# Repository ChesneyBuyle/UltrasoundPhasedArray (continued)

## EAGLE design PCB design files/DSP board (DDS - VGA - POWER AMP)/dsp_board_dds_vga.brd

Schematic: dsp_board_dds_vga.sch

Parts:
C1, C2, C3, C8, C13, C14, C19, C20, C25, C26, C31, C32, C37, C38, C43, C44, C49, C50, C55, C56, C61, C62, C67, C68, C73, C74, C79, C80, C86, C91, C92, C97, C98, C106, C113, C119, C121, C127, C129, C135, C137, C143, C145, C151, C153, C159, C161, C167, C169, C175, C177, C183, C185, C191, C193, C199, C201, C207, C209, C215, C217, C223, C225, C231: 0.1u; C0603
C4, C5, C9, C10, C15, C16, C21, C22, C27, C28, C33, C34, C39, C40, C45, C46, C51, C52, C57, C58, C63, C64, C69, C70, C75, C76, C81, C82, C93, C94, C99, C100: 10n; C0603
C6, C11, C17, C23, C29, C35, C41, C47, C53, C59, C65, C71, C77, C83, C95, C101: 20p; C0603
C7, C12, C18, C24, C30, C36, C42, C48, C54, C60, C66, C72, C78, C84, C96, C102: TBD; C0603
C87, C88, C89, C90, C107, C114, C115, C116, C117, C120, C122, C123, C124, C125, C128, C130, C131, C132, C133, C136, C138, C139, C140, C141, C144, C146, C147, C148, C149, C152, C154, C155, C156, C157, C160, C162, C163, C164, C165, C168, C170, C171, C172, C173, C176, C178, C179, C180, C181, C184, C186, C187, C188, C189, C192, C194, C195, C196, C197, C200, C202, C203, C204, C205, C208, C210, C211, C212, C213, C216, C218, C219, C220, C221, C224, C226, C227, C228, C229, C232: 1u; C0603
C104, C118, C126, C134, C142, C150, C158, C166, C174, C182, C190, C198, C206, C214, C222, C230: 10u; C0805
H1, H2: MOUNT-HOLE3.0; 3,0
IC1, IC2, IC3, IC4, IC5, IC6, IC7, IC8, IC9, IC10, IC11, IC12, IC13, IC14, IC16, IC17: AD9834; TSSOP20
J1, J4: 6130XX21021_61301421021; 61301421021
J2, J7: 6130XX21021_61301621021; 61301621021
JP1, JP2, JP3, JP4, JP5, JP6, JP7, JP8, JP9, JP10, JP11, JP12, JP13, JP14, JP15, JP16: PINHD-1X2; 1X02
LDO, LDO2, LDO3, LDO4, LDO5, LDO6, LDO7, LDO8, LDO9, LDO10, LDO11, LDO12, LDO13, LDO14, LDO15, LDO16: TLV75525PDBVR; SOT95P280X145-5N
LSP1, LSP2, LSP3, LSP4, LSP5, LSP6, LSP7, LSP8, LSP9, LSP10, LSP11, LSP12, LSP13, LSP14, LSP15, LSP16, LSP17, LSP18, LSP19, LSP20: LSP10
R1, R2, R9, R13, R17, R21, R25, R29, R33, R37, R41, R45, R49, R53, R61, R65: 6.8k; R0603
R3, R8, R12, R16, R20, R24, R28, R32, R36, R40, R44, R48, R52, R56, R64, R68: TBD; R0603
R4, R5, R6, R7, R10, R11, R14, R15, R18, R19, R22, R23, R26, R27, R30, R31, R34, R35, R38, R39, R42, R43, R46, R47, R50, R51, R54, R55, R62, R63, R66, R67: 200; R0603
R57, R59, R60, R69, R70, R71, R72, R73, R74, R75, R76, R77, R78, R79, R80, R81: R-EU_R0603; R0603
SJ1, SJ2, SJ3, SJ4, SJ5, SJ6, SJ7, SJ8, SJ9, SJ10, SJ11, SJ12, SJ13, SJ14, SJ15, SJ16, SJ17, SJ18, SJ19, SJ20, SJ21, SJ22, SJ23, SJ24, SJ25, SJ26, SJ27, SJ28, SJ29, SJ30, SJ31, SJ32, SJ33, SJ34, SJ35, SJ36, SJ37, SJ38, SJ39, SJ40, SJ41, SJ42, SJ43, SJ44, SJ45, SJ46, SJ47, SJ48, SJ49, SJ50, SJ51, SJ52, SJ53, SJ54, SJ55, SJ56, SJ57, SJ58, SJ59, SJ60, SJ61, SJ62, SJ63, SJ64, SJ65, SJ66, SJ67, SJ68, SJ69, SJ70, SJ71, SJ72, SJ73, SJ74, SJ75, SJ76, SJ77, SJ78, SJ79, SJ80, SJ81, SJ82, SJ83, SJ84, SJ91, SJ92, SJ93, SJ94, SJ95, SJ96, SJ97, SJ98, SJ99, SJ100, SJ101, SJ102: SJ
U1, U7, U10, U13, U16, U19, U22, U25, U28, U31, U34, U37, U40, U43, U46, U49: TPS60400DBVT; SOT95P280X145-5N
U2, U9, U12, U15, U18, U21, U24, U27, U30, U33, U36, U39, U42, U45, U48, U51: TLV271CDBVR; SOT95P280X145-5N
U3, U8, U11, U14, U17, U20, U23, U26, U29, U32, U35, U38, U41, U44, U47, U50: AD5270BRMZ-50; SOP50P490X110-10N

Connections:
2.5V_1: C86.2, C89.2, C104.1, LDO.5 (OUT), U1.2 (IN), U2.5 (VDD), U3.1 (VDD)
2.5V_2: C113.2, C116.2, C118.1, LDO2.5 (OUT), U7.2 (IN), U8.1 (VDD), U9.5 (VDD)
2.5V_3: C137.2, C140.2, C142.1, LDO5.5 (OUT), U16.2 (IN), U17.1 (VDD), U18.5 (VDD)
2.5V_4: C145.2, C148.2, C150.1, LDO6.5 (OUT), U19.2 (IN), U20.1 (VDD), U21.5 (VDD)
2.5V_5: C121.2, C124.2, C126.1, LDO3.5 (OUT), U10.2 (IN), U11.1 (VDD), U12.5 (VDD)
2.5V_6: C129.2, C132.2, C134.1, LDO4.5 (OUT), U13.2 (IN), U14.1 (VDD), U15.5 (VDD)
2.5V_7: C153.2, C156.2, C158.1, LDO7.5 (OUT), U22.2 (IN), U23.1 (VDD), U24.5 (VDD)
2.5V_8: C161.2, C164.2, C166.1, LDO8.5 (OUT), U25.2 (IN), U26.1 (VDD), U27.5 (VDD)
2.5V_9: C169.2, C172.2, C174.1, LDO9.5 (OUT), U28.2 (IN), U29.1 (VDD), U30.5 (VDD)
2.5V_10: C177.2, C180.2, C182.1, LDO10.5 (OUT), U31.2 (IN), U32.1 (VDD), U33.5 (VDD)
2.5V_11: C201.2, C204.2, C206.1, LDO13.5 (OUT), U40.2 (IN), U41.1 (VDD), U42.5 (VDD)
2.5V_12: C209.2, C212.2, C214.1, LDO14.5 (OUT), U43.2 (IN), U44.1 (VDD), U45.5 (VDD)
2.5V_13: C185.2, C188.2, C190.1, LDO11.5 (OUT), U34.2 (IN), U35.1 (VDD), U36.5 (VDD)
2.5V_14: C193.2, C196.2, C198.1, LDO12.5 (OUT), U37.2 (IN), U38.1 (VDD), U39.5 (VDD)
2.5V_15: C217.2, C220.2, C222.1, LDO15.5 (OUT), U46.2 (IN), U47.1 (VDD), U48.5 (VDD)
2.5V_16: C225.2, C228.2, C230.1, LDO16.5 (OUT), U49.2 (IN), U50.1 (VDD), U51.5 (VDD)
+3V3: C1.1, C2.1, C5.2, C10.2, C13.1, C16.2, C19.1, C22.2, C25.1, C28.2, C31.1, C34.2, C37.1, C40.2, C43.1, C46.2, C49.1, C52.2, C55.1, C58.2, C61.1, C64.2, C67.1, C70.2, C73.1, C76.2, C79.1, C82.2, C87.2, C91.1, C94.2, C97.1, C100.2, C114.2, C122.2, C130.2, C138.2, C146.2, C154.2, C162.2, C170.2, C178.2, C186.2, C194.2, C202.2, C210.2, C218.2, C226.2, IC1.4 (AVDD), IC1.5 (DVDD), IC2.4 (AVDD), IC2.5 (DVDD), IC3.4 (AVDD), IC3.5 (DVDD), IC4.4 (AVDD), IC4.5 (DVDD), IC5.4 (AVDD), IC5.5 (DVDD), IC6.4 (AVDD), IC6.5 (DVDD), IC7.4 (AVDD), IC7.5 (DVDD), IC8.4 (AVDD), IC8.5 (DVDD), IC9.4 (AVDD), IC9.5 (DVDD), IC10.4 (AVDD), IC10.5 (DVDD), IC11.4 (AVDD), IC11.5 (DVDD), IC12.4 (AVDD), IC12.5 (DVDD), IC13.4 (AVDD), IC13.5 (DVDD), IC14.4 (AVDD), IC14.5 (DVDD), IC16.4 (AVDD), IC16.5 (DVDD), IC17.4 (AVDD), IC17.5 (DVDD), J2.1, J7.1, LDO.1 (IN), LDO.3 (EN), LDO2.1 (IN), LDO2.3 (EN), LDO3.1 (IN), LDO3.3 (EN), LDO4.1 (IN), LDO4.3 (EN), LDO5.1 (IN), LDO5.3 (EN), LDO6.1 (IN), LDO6.3 (EN), LDO7.1 (IN), LDO7.3 (EN), LDO8.1 (IN), LDO8.3 (EN), LDO9.1 (IN), LDO9.3 (EN), LDO10.1 (IN), LDO10.3 (EN), LDO11.1 (IN), LDO11.3 (EN), LDO12.1 (IN), LDO12.3 (EN), LDO13.1 (IN), LDO13.3 (EN), LDO14.1 (IN), LDO14.3 (EN), LDO15.1 (IN), LDO15.3 (EN), LDO16.1 (IN), LDO16.3 (EN)
DDS1_OUT: R57.1, SJ1.2, SJ2.2
DDS2_OUT: R59.1, SJ6.2, SJ8.2
DDS3_OUT: R70.1, SJ13.2, SJ14.2
DDS4_OUT: R71.1, SJ19.2, SJ20.2
DDS5_OUT: R60.1, SJ25.2, SJ26.2
DDS6_OUT: R69.1, SJ31.2, SJ32.2
DDS7_OUT: R72.1, SJ37.2, SJ38.2
DDS8_OUT: R73.1, SJ43.2, SJ44.2
DDS9_OUT: R74.1, SJ49.2, SJ50.2
DDS10_OUT: R75.1, SJ55.2, SJ56.2
DDS11_OUT: R78.1, SJ61.2, SJ62.2
DDS12_OUT: R79.1, SJ67.2, SJ68.2
DDS13_OUT: R76.1, SJ73.2, SJ74.2
DDS14_OUT: R77.1, SJ91.2, SJ92.2
DDS15_OUT: R80.1, SJ79.2, SJ80.2
DDS16_OUT: R81.1, SJ97.2, SJ98.2
DIN_2_A: J2.12, U3.8 (DIN), U8.8 (DIN), U17.8 (DIN), U20.8 (DIN)
DIN_2_B: J4.10, U11.8 (DIN), U14.8 (DIN), U23.8 (DIN), U26.8 (DIN)
DIN_2_C: J1.10, U29.8 (DIN), U32.8 (DIN), U41.8 (DIN), U44.8 (DIN)
DIN_2_D: J7.12, U35.8 (DIN), U38.8 (DIN), U47.8 (DIN), U50.8 (DIN)
FILTER1: C7.1, R3.2, SJ1.1, SJ4.2, SJ5.2
FILTER2: C12.1, R8.2, SJ6.1, SJ11.2, SJ12.2
FILTER3: C18.1, R12.2, SJ13.1, SJ17.2, SJ18.2
FILTER4: C24.1, R16.2, SJ19.1, SJ23.2, SJ24.2
FILTER5: C30.1, R20.2, SJ25.1, SJ29.2, SJ30.2
FILTER6: C36.1, R24.2, SJ31.1, SJ35.2, SJ36.2
FILTER7: C42.1, R28.2, SJ37.1, SJ41.2, SJ42.2
FILTER8: C48.1, R32.2, SJ43.1, SJ47.2, SJ48.2
FILTER9: C54.1, R36.2, SJ49.1, SJ53.2, SJ54.2
FILTER10: C60.1, R40.2, SJ55.1, SJ59.2, SJ60.2
FILTER11: C66.1, R44.2, SJ61.1, SJ65.2, SJ66.2
FILTER12: C72.1, R48.2, SJ67.1, SJ71.2, SJ72.2
FILTER13: C78.1, R52.2, SJ73.1, SJ77.2, SJ78.2
FILTER14: C96.1, R64.2, SJ91.1, SJ95.2, SJ96.2
FILTER15: C84.1, R56.2, SJ79.1, SJ83.2, SJ84.2
FILTER16: C102.1, R68.2, SJ97.1, SJ101.2, SJ102.2
FSELECT_A: IC1.9 (FSELECT), IC2.9 (FSELECT), IC3.9 (FSELECT), IC4.9 (FSELECT), J2.3
FSELECT_B: IC5.9 (FSELECT), IC6.9 (FSELECT), IC7.9 (FSELECT), IC8.9 (FSELECT), J4.1
FSELECT_C: IC9.9 (FSELECT), IC10.9 (FSELECT), IC11.9 (FSELECT), IC12.9 (FSELECT), J1.1
FSELECT_D: IC13.9 (FSELECT), IC14.9 (FSELECT), IC16.9 (FSELECT), IC17.9 (FSELECT), J7.3
FSYNC1: IC1.15 (FSYNC), J2.5, U3.10 (~SYNC)
FSYNC2: IC2.15 (FSYNC), J2.8, U8.10 (~SYNC)
FSYNC3: IC3.15 (FSYNC), J2.7, U17.10 (~SYNC)
FSYNC4: IC4.15 (FSYNC), J2.10, U20.10 (~SYNC)
FSYNC5: IC5.15 (FSYNC), J4.3, U11.10 (~SYNC)
FSYNC6: IC6.15 (FSYNC), J4.6, U14.10 (~SYNC)
FSYNC7: IC7.15 (FSYNC), J4.5, U23.10 (~SYNC)
FSYNC8: IC8.15 (FSYNC), J4.8, U26.10 (~SYNC)
FSYNC9: IC9.15 (FSYNC), J1.3, U29.10 (~SYNC)
FSYNC10: IC10.15 (FSYNC), J1.6, U32.10 (~SYNC)
FSYNC11: IC11.15 (FSYNC), J1.5, U41.10 (~SYNC)
FSYNC12: IC12.15 (FSYNC), J1.8, U44.10 (~SYNC)
FSYNC13: IC13.15 (FSYNC), J7.5, U35.10 (~SYNC)
FSYNC14: IC16.15 (FSYNC), J7.8, U38.10 (~SYNC)
FSYNC15: IC14.15 (FSYNC), J7.7, U47.10 (~SYNC)
FSYNC16: IC17.15 (FSYNC), J7.10, U50.10 (~SYNC)
GND: C1.2, C2.2, C3.2, C4.2, C6.2, C7.2, C8.2, C9.2, C11.2, C12.2, C13.2, C14.2, C15.2, C17.2, C18.2, C19.2, C20.2, C21.2, C23.2, C24.2, C25.2, C26.2, C27.2, C29.2, C30.2, C31.2, C32.2, C33.2, C35.2, C36.2, C37.2, C38.2, C39.2, C41.2, C42.2, C43.2, C44.2, C45.2, C47.2, C48.2, C49.2, C50.2, C51.2, C53.2, C54.2, C55.2, C56.2, C57.2, C59.2, C60.2, C61.2, C62.2, C63.2, C65.2, C66.2, C67.2, C68.2, C69.2, C71.2, C72.2, C73.2, C74.2, C75.2, C77.2, C78.2, C79.2, C80.2, C81.2, C83.2, C84.2, C86.1, C87.1, C89.1, C90.1, C91.2, C92.2, C93.2, C95.2, C96.2, C97.2, C98.2, C99.2, C101.2, C102.2, C104.2, C106.2, C107.2, C113.1, C114.1, C116.1, C117.1, C118.2, C119.2, C120.2, C121.1, C122.1, C124.1, C125.1, C126.2, C127.2, C128.2, C129.1, C130.1, C132.1, C133.1, C134.2, C135.2, C136.2, C137.1, C138.1, C140.1, C141.1, C142.2, C143.2, C144.2, C145.1, C146.1, C148.1, C149.1, C150.2, C151.2, C152.2, C153.1, C154.1, C156.1, C157.1, C158.2, C159.2, C160.2, C161.1, C162.1, C164.1, C165.1, C166.2, C167.2, C168.2, C169.1, C170.1, C172.1, C173.1, C174.2, C175.2, C176.2, C177.1, C178.1, C180.1, C181.1, C182.2, C183.2, C184.2, C185.1, C186.1, C188.1, C189.1, C190.2, C191.2, C192.2, C193.1, C194.1, C196.1, C197.1, C198.2, C199.2, C200.2, C201.1, C202.1, C204.1, C205.1, C206.2, C207.2, C208.2, C209.1, C210.1, C212.1, C213.1, C214.2, C215.2, C216.2, C217.1, C218.1, C220.1, C221.1, C222.2, C223.2, C224.2, C225.1, C226.1, C228.1, C229.1, C230.2, C231.2, C232.2, IC1.7 (DGND), IC1.18 (AGND), IC2.7 (DGND), IC2.18 (AGND), IC3.7 (DGND), IC3.18 (AGND), IC4.7 (DGND), IC4.18 (AGND), IC5.7 (DGND), IC5.18 (AGND), IC6.7 (DGND), IC6.18 (AGND), IC7.7 (DGND), IC7.18 (AGND), IC8.7 (DGND), IC8.18 (AGND), IC9.7 (DGND), IC9.18 (AGND), IC10.7 (DGND), IC10.18 (AGND), IC11.7 (DGND), IC11.18 (AGND), IC12.7 (DGND), IC12.18 (AGND), IC13.7 (DGND), IC13.18 (AGND), IC14.7 (DGND), IC14.18 (AGND), IC16.7 (DGND), IC16.18 (AGND), IC17.7 (DGND), IC17.18 (AGND), J2.2, J7.2, JP1.2, JP2.2, JP3.2, JP4.2, JP5.2, JP6.2, JP7.2, JP8.2, JP9.2, JP10.2, JP11.2, JP12.2, JP13.2, JP14.2, JP15.2, JP16.2, LDO.2 (GND), LDO2.2 (GND), LDO3.2 (GND), LDO4.2 (GND), LDO5.2 (GND), LDO6.2 (GND), LDO7.2 (GND), LDO8.2 (GND), LDO9.2 (GND), LDO10.2 (GND), LDO11.2 (GND), LDO12.2 (GND), LDO13.2 (GND), LDO14.2 (GND), LDO15.2 (GND), LDO16.2 (GND), LSP1.MP, LSP2.MP, LSP3.MP, LSP4.MP, LSP5.MP, LSP6.MP, LSP7.MP, LSP8.MP, LSP9.MP, LSP10.MP, LSP11.MP, LSP12.MP, LSP13.MP, LSP14.MP, LSP15.MP, LSP16.MP, LSP17.MP, LSP18.MP, LSP19.MP, LSP20.MP, R1.2, R2.2, R4.1, R5.1, R6.1, R7.1, R9.2, R10.1, R11.1, R13.2, R14.1, R15.1, R17.2, R18.1, R19.1, R21.2, R22.1, R23.1, R25.2, R26.1, R27.1, R29.2, R30.1, R31.1, R33.2, R34.1, R35.1, R37.2, R38.1, R39.1, R41.2, R42.1, R43.1, R45.2, R46.1, R47.1, R49.2, R50.1, R51.1, R53.2, R54.1, R55.1, R61.2, R62.1, R63.1, R65.2, R66.1, R67.1, SJ3.1, SJ7.2, SJ9.1, SJ10.2, SJ15.1, SJ16.2, SJ21.1, SJ22.2, SJ27.1, SJ28.2, SJ33.1, SJ34.2, SJ39.1, SJ40.2, SJ45.1, SJ46.2, SJ51.1, SJ52.2, SJ57.1, SJ58.2, SJ63.1, SJ64.2, SJ69.1, SJ70.2, SJ75.1, SJ76.2, SJ81.1, SJ82.2, SJ93.1, SJ94.2, SJ99.1, SJ100.2, U1.4 (GND), U2.3 (IN+), U3.6 (GND), U7.4 (GND), U8.6 (GND), U9.3 (IN+), U10.4 (GND), U11.6 (GND), U12.3 (IN+), U13.4 (GND), U14.6 (GND), U15.3 (IN+), U16.4 (GND), U17.6 (GND), U18.3 (IN+), U19.4 (GND), U20.6 (GND), U21.3 (IN+), U22.4 (GND), U23.6 (GND), U24.3 (IN+), U25.4 (GND), U26.6 (GND), U27.3 (IN+), U28.4 (GND), U29.6 (GND), U30.3 (IN+), U31.4 (GND), U32.6 (GND), U33.3 (IN+), U34.4 (GND), U35.6 (GND), U36.3 (IN+), U37.4 (GND), U38.6 (GND), U39.3 (IN+), U40.4 (GND), U41.6 (GND), U42.3 (IN+), U43.4 (GND), U44.6 (GND), U45.3 (IN+), U46.4 (GND), U47.6 (GND), U48.3 (IN+), U49.4 (GND), U50.6 (GND), U51.3 (IN+)
IOUT1: IC1.19 (IOUT), R3.1, R5.2, SJ4.1
IOUT2: IC2.19 (IOUT), R7.2, R8.1, SJ11.1
IOUT3: IC3.19 (IOUT), R11.2, R12.1, SJ17.1
IOUT4: IC4.19 (IOUT), R15.2, R16.1, SJ23.1
IOUT5: IC5.19 (IOUT), R19.2, R20.1, SJ29.1
IOUT6: IC6.19 (IOUT), R23.2, R24.1, SJ35.1
IOUT7: IC7.19 (IOUT), R27.2, R28.1, SJ41.1
IOUT8: IC8.19 (IOUT), R31.2, R32.1, SJ47.1
IOUT9: IC9.19 (IOUT), R35.2, R36.1, SJ53.1
IOUT10: IC10.19 (IOUT), R39.2, R40.1, SJ59.1
IOUT11: IC11.19 (IOUT), R43.2, R44.1, SJ65.1
IOUT12: IC12.19 (IOUT), R47.2, R48.1, SJ71.1
IOUT13: IC13.19 (IOUT), R51.2, R52.1, SJ77.1
IOUT14: IC16.19 (IOUT), R63.2, R64.1, SJ95.1
IOUT15: IC14.19 (IOUT), R55.2, R56.1, SJ83.1
IOUT16: IC17.19 (IOUT), R67.2, R68.1, SJ101.1
IOUTB1: C6.1, IC1.20 (IOUTB), R4.2, SJ7.1
IOUTB2: C11.1, IC2.20 (IOUTB), R6.2, SJ10.1
IOUTB3: C17.1, IC3.20 (IOUTB), R10.2, SJ16.1
IOUTB4: C23.1, IC4.20 (IOUTB), R14.2, SJ22.1
IOUTB5: C29.1, IC5.20 (IOUTB), R18.2, SJ28.1
IOUTB6: C35.1, IC6.20 (IOUTB), R22.2, SJ34.1
IOUTB7: C41.1, IC7.20 (IOUTB), R26.2, SJ40.1
IOUTB8: C47.1, IC8.20 (IOUTB), R30.2, SJ46.1
IOUTB9: C53.1, IC9.20 (IOUTB), R34.2, SJ52.1
IOUTB10: C59.1, IC10.20 (IOUTB), R38.2, SJ58.1
IOUTB11: C65.1, IC11.20 (IOUTB), R42.2, SJ64.1
IOUTB12: C71.1, IC12.20 (IOUTB), R46.2, SJ70.1
IOUTB13: C77.1, IC13.20 (IOUTB), R50.2, SJ76.1
IOUTB14: C95.1, IC16.20 (IOUTB), R62.2, SJ94.1
IOUTB15: C83.1, IC14.20 (IOUTB), R54.2, SJ82.1
IOUTB16: C101.1, IC17.20 (IOUTB), R66.2, SJ100.1
MCLK_A: IC1.8 (MCLK), IC2.8 (MCLK), IC3.8 (MCLK), IC4.8 (MCLK), J2.6
MCLK_B: IC5.8 (MCLK), IC6.8 (MCLK), IC7.8 (MCLK), IC8.8 (MCLK), J4.4
MCLK_C: IC9.8 (MCLK), IC10.8 (MCLK), IC11.8 (MCLK), IC12.8 (MCLK), J1.4
MCLK_D: IC13.8 (MCLK), IC14.8 (MCLK), IC16.8 (MCLK), IC17.8 (MCLK), J7.6
unnamed: C3.1, IC1.6 (CAP/2,5V)
unnamed: IC1.1 (FS_ADJUST), R1.1
unnamed: C4.1, IC1.2 (REFOUT)
unnamed: C5.1, IC1.3 (COMP)
unnamed: IC1.17 (VIN), SJ3.2, SJ5.1
unnamed: C8.1, IC2.6 (CAP/2,5V)
unnamed: IC2.1 (FS_ADJUST), R2.1
unnamed: C9.1, IC2.2 (REFOUT)
unnamed: C10.1, IC2.3 (COMP)
unnamed: IC2.17 (VIN), SJ9.2, SJ12.1
unnamed: C14.1, IC3.6 (CAP/2,5V)
unnamed: IC3.1 (FS_ADJUST), R9.1
unnamed: C15.1, IC3.2 (REFOUT)
unnamed: C16.1, IC3.3 (COMP)
unnamed: IC3.17 (VIN), SJ15.2, SJ18.1
unnamed: C20.1, IC4.6 (CAP/2,5V)
unnamed: IC4.1 (FS_ADJUST), R13.1
unnamed: C21.1, IC4.2 (REFOUT)
unnamed: C22.1, IC4.3 (COMP)
unnamed: IC4.17 (VIN), SJ21.2, SJ24.1
unnamed: C26.1, IC5.6 (CAP/2,5V)
unnamed: IC5.1 (FS_ADJUST), R17.1
unnamed: C27.1, IC5.2 (REFOUT)
unnamed: C28.1, IC5.3 (COMP)
unnamed: IC5.17 (VIN), SJ27.2, SJ30.1
unnamed: C32.1, IC6.6 (CAP/2,5V)
unnamed: IC6.1 (FS_ADJUST), R21.1
unnamed: C33.1, IC6.2 (REFOUT)
unnamed: C34.1, IC6.3 (COMP)
unnamed: IC6.17 (VIN), SJ33.2, SJ36.1
unnamed: C38.1, IC7.6 (CAP/2,5V)
unnamed: IC7.1 (FS_ADJUST), R25.1
unnamed: C39.1, IC7.2 (REFOUT)
unnamed: C40.1, IC7.3 (COMP)
unnamed: IC7.17 (VIN), SJ39.2, SJ42.1
unnamed: C44.1, IC8.6 (CAP/2,5V)
unnamed: IC8.1 (FS_ADJUST), R29.1
unnamed: C45.1, IC8.2 (REFOUT)
unnamed: C46.1, IC8.3 (COMP)
unnamed: IC8.17 (VIN), SJ45.2, SJ48.1
unnamed: C50.1, IC9.6 (CAP/2,5V)
unnamed: IC9.1 (FS_ADJUST), R33.1
unnamed: C51.1, IC9.2 (REFOUT)
unnamed: C52.1, IC9.3 (COMP)
unnamed: IC9.17 (VIN), SJ51.2, SJ54.1
unnamed: C56.1, IC10.6 (CAP/2,5V)
unnamed: IC10.1 (FS_ADJUST), R37.1
unnamed: C57.1, IC10.2 (REFOUT)
unnamed: C58.1, IC10.3 (COMP)
unnamed: IC10.17 (VIN), SJ57.2, SJ60.1
unnamed: C62.1, IC11.6 (CAP/2,5V)
unnamed: IC11.1 (FS_ADJUST), R41.1
unnamed: C63.1, IC11.2 (REFOUT)
unnamed: C64.1, IC11.3 (COMP)
unnamed: IC11.17 (VIN), SJ63.2, SJ66.1
unnamed: C68.1, IC12.6 (CAP/2,5V)
unnamed: IC12.1 (FS_ADJUST), R45.1
unnamed: C69.1, IC12.2 (REFOUT)
unnamed: C70.1, IC12.3 (COMP)
unnamed: IC12.17 (VIN), SJ69.2, SJ72.1
unnamed: C74.1, IC13.6 (CAP/2,5V)
unnamed: IC13.1 (FS_ADJUST), R49.1
unnamed: C75.1, IC13.2 (REFOUT)
unnamed: C76.1, IC13.3 (COMP)
unnamed: IC13.17 (VIN), SJ75.2, SJ78.1
unnamed: C80.1, IC14.6 (CAP/2,5V)
unnamed: IC14.1 (FS_ADJUST), R53.1
unnamed: C81.1, IC14.2 (REFOUT)
unnamed: C82.1, IC14.3 (COMP)
unnamed: IC14.17 (VIN), SJ81.2, SJ84.1
unnamed: C92.1, IC16.6 (CAP/2,5V)
unnamed: IC16.1 (FS_ADJUST), R61.1
unnamed: C93.1, IC16.2 (REFOUT)
unnamed: C94.1, IC16.3 (COMP)
unnamed: IC16.17 (VIN), SJ93.2, SJ96.1
unnamed: C98.1, IC17.6 (CAP/2,5V)
unnamed: IC17.1 (FS_ADJUST), R65.1
unnamed: C99.1, IC17.2 (REFOUT)
unnamed: C100.1, IC17.3 (COMP)
unnamed: IC17.17 (VIN), SJ99.2, SJ102.1
unnamed: C88.2, U1.5 (CFLY+)
unnamed: C88.1, U1.3 (CFLY-)
unnamed: C107.1, U3.5 (EXT_CAP)
unnamed: C115.2, U7.5 (CFLY+)
unnamed: C115.1, U7.3 (CFLY-)
unnamed: C120.1, U8.5 (EXT_CAP)
unnamed: C211.2, U43.5 (CFLY+)
unnamed: C163.2, U25.5 (CFLY+)
unnamed: C123.2, U10.5 (CFLY+)
unnamed: C123.1, U10.3 (CFLY-)
unnamed: C128.1, U11.5 (EXT_CAP)
unnamed: C131.2, U13.5 (CFLY+)
unnamed: C131.1, U13.3 (CFLY-)
unnamed: C136.1, U14.5 (EXT_CAP)
unnamed: C139.2, U16.5 (CFLY+)
unnamed: C139.1, U16.3 (CFLY-)
unnamed: C144.1, U17.5 (EXT_CAP)
unnamed: C147.2, U19.5 (CFLY+)
unnamed: C147.1, U19.3 (CFLY-)
unnamed: C152.1, U20.5 (EXT_CAP)
unnamed: C155.2, U22.5 (CFLY+)
unnamed: C155.1, U22.3 (CFLY-)
unnamed: C160.1, U23.5 (EXT_CAP)
unnamed: C163.1, U25.3 (CFLY-)
unnamed: C168.1, U26.5 (EXT_CAP)
unnamed: C211.1, U43.3 (CFLY-)
unnamed: C187.2, U34.5 (CFLY+)
unnamed: C179.2, U31.5 (CFLY+)
unnamed: C171.2, U28.5 (CFLY+)
unnamed: C171.1, U28.3 (CFLY-)
unnamed: C176.1, U29.5 (EXT_CAP)
unnamed: C179.1, U31.3 (CFLY-)
unnamed: C184.1, U32.5 (EXT_CAP)
unnamed: C187.1, U34.3 (CFLY-)
unnamed: C192.1, U35.5 (EXT_CAP)
unnamed: C195.2, U37.5 (CFLY+)
unnamed: C195.1, U37.3 (CFLY-)
unnamed: C200.1, U38.5 (EXT_CAP)
unnamed: C203.2, U40.5 (CFLY+)
unnamed: C203.1, U40.3 (CFLY-)
unnamed: C208.1, U41.5 (EXT_CAP)
unnamed: C216.1, U44.5 (EXT_CAP)
unnamed: C219.2, U46.5 (CFLY+)
unnamed: C219.1, U46.3 (CFLY-)
unnamed: C224.1, U47.5 (EXT_CAP)
unnamed: C227.2, U49.5 (CFLY+)
unnamed: C227.1, U49.3 (CFLY-)
unnamed: C232.1, U50.5 (EXT_CAP)
POT_A_1: R57.2, U2.4 (IN-), U3.2 (A)
POT_A_2: R59.2, U8.2 (A), U9.4 (IN-)
POT_A_3: R70.2, U17.2 (A), U18.4 (IN-)
POT_A_4: R71.2, U20.2 (A), U21.4 (IN-)
POT_A_5: R60.2, U11.2 (A), U12.4 (IN-)
POT_A_6: R69.2, U14.2 (A), U15.4 (IN-)
POT_A_7: R72.2, U23.2 (A), U24.4 (IN-)
POT_A_8: R73.2, U26.2 (A), U27.4 (IN-)
POT_A_9: R74.2, U29.2 (A), U30.4 (IN-)
POT_A_10: R75.2, U32.2 (A), U33.4 (IN-)
POT_A_11: R78.2, U41.2 (A), U42.4 (IN-)
POT_A_12: R79.2, U44.2 (A), U45.4 (IN-)
POT_A_13: R76.2, U35.2 (A), U36.4 (IN-)
POT_A_14: R77.2, U38.2 (A), U39.4 (IN-)
POT_A_15: R80.2, U47.2 (A), U48.4 (IN-)
POT_A_16: R81.2, U50.2 (A), U51.4 (IN-)
POT_W_1: JP3.1, U2.1 (OUT), U3.3 (W)
POT_W_2: JP4.1, U8.3 (W), U9.1 (OUT)
POT_W_3: JP6.1, U17.3 (W), U18.1 (OUT)
POT_W_4: JP7.1, U20.3 (W), U21.1 (OUT)
POT_W_5: JP1.1, U11.3 (W), U12.1 (OUT)
POT_W_6: JP2.1, U14.3 (W), U15.1 (OUT)
POT_W_7: JP5.1, U23.3 (W), U24.1 (OUT)
POT_W_8: JP8.1, U26.3 (W), U27.1 (OUT)
POT_W_9: JP9.1, U29.3 (W), U30.1 (OUT)
POT_W_10: JP10.1, U32.3 (W), U33.1 (OUT)
POT_W_11: JP11.1, U41.3 (W), U42.1 (OUT)
POT_W_12: JP12.1, U44.3 (W), U45.1 (OUT)
POT_W_13: JP13.1, U35.3 (W), U36.1 (OUT)
POT_W_14: JP14.1, U38.3 (W), U39.1 (OUT)
POT_W_15: JP15.1, U47.3 (W), U48.1 (OUT)
POT_W_16: JP16.1, U50.3 (W), U51.1 (OUT)
PSELECT_A: IC1.10 (PSELECT), IC2.10 (PSELECT), IC3.10 (PSELECT), IC4.10 (PSELECT), J2.4
PSELECT_B: IC5.10 (PSELECT), IC6.10 (PSELECT), IC7.10 (PSELECT), IC8.10 (PSELECT), J4.2
PSELECT_C: IC9.10 (PSELECT), IC10.10 (PSELECT), IC11.10 (PSELECT), IC12.10 (PSELECT), J1.2
PSELECT_D: IC13.10 (PSELECT), IC14.10 (PSELECT), IC16.10 (PSELECT), IC17.10 (PSELECT), J7.4
RESET_A: IC1.11 (RESET), IC2.11 (RESET), IC3.11 (RESET), IC4.11 (RESET), J2.16
RESET_B: IC5.11 (RESET), IC6.11 (RESET), IC7.11 (RESET), IC8.11 (RESET), J4.14
RESET_C: IC9.11 (RESET), IC10.11 (RESET), IC11.11 (RESET), IC12.11 (RESET), J1.14
RESET_D: IC13.11 (RESET), IC14.11 (RESET), IC16.11 (RESET), IC17.11 (RESET), J7.16
SCLK2_A: J2.11, U3.9 (SCLK), U8.9 (SCLK), U17.9 (SCLK), U20.9 (SCLK)
SCLK2_B: J4.9, U11.9 (SCLK), U14.9 (SCLK), U23.9 (SCLK), U26.9 (SCLK)
SCLK2_C: J1.9, U29.9 (SCLK), U32.9 (SCLK), U41.9 (SCLK), U44.9 (SCLK)
SCLK2_D: J7.11, U35.9 (SCLK), U38.9 (SCLK), U47.9 (SCLK), U50.9 (SCLK)
SCLK_1_A: IC1.14 (SCLK), IC2.14 (SCLK), IC3.14 (SCLK), IC4.14 (SCLK), J2.13
SCLK_1_B: IC5.14 (SCLK), IC6.14 (SCLK), IC7.14 (SCLK), IC8.14 (SCLK), J4.11
SCLK_1_C: IC9.14 (SCLK), IC10.14 (SCLK), IC11.14 (SCLK), IC12.14 (SCLK), J1.11
SCLK_1_D: IC13.14 (SCLK), IC14.14 (SCLK), IC16.14 (SCLK), IC17.14 (SCLK), J7.13
SDATA_1_A: IC1.13 (SDATA), IC2.13 (SDATA), IC3.13 (SDATA), IC4.13 (SDATA), J2.14
SDATA_1_B: IC5.13 (SDATA), IC6.13 (SDATA), IC7.13 (SDATA), IC8.13 (SDATA), J4.12
SDATA_1_C: IC9.13 (SDATA), IC10.13 (SDATA), IC11.13 (SDATA), IC12.13 (SDATA), J1.12
SDATA_1_D: IC13.13 (SDATA), IC14.13 (SDATA), IC16.13 (SDATA), IC17.13 (SDATA), J7.14
SDO_2_A: J2.9, U3.7 (SDO), U8.7 (SDO), U17.7 (SDO), U20.7 (SDO)
SDO_2_B: J4.7, U11.7 (SDO), U14.7 (SDO), U23.7 (SDO), U26.7 (SDO)
SDO_2_C: J1.7, U29.7 (SDO), U32.7 (SDO), U41.7 (SDO), U44.7 (SDO)
SDO_2_D: J7.9, U35.7 (SDO), U38.7 (SDO), U47.7 (SDO), U50.7 (SDO)
SIGN_BIT_OUT1: IC1.16 (SIGN_BIT_OUT), SJ2.1
SIGN_BIT_OUT2: IC2.16 (SIGN_BIT_OUT), SJ8.1
SIGN_BIT_OUT3: IC3.16 (SIGN_BIT_OUT), SJ14.1
SIGN_BIT_OUT4: IC4.16 (SIGN_BIT_OUT), SJ20.1
SIGN_BIT_OUT5: IC5.16 (SIGN_BIT_OUT), SJ26.1
SIGN_BIT_OUT6: IC6.16 (SIGN_BIT_OUT), SJ32.1
SIGN_BIT_OUT7: IC7.16 (SIGN_BIT_OUT), SJ38.1
SIGN_BIT_OUT8: IC8.16 (SIGN_BIT_OUT), SJ44.1
SIGN_BIT_OUT9: IC9.16 (SIGN_BIT_OUT), SJ50.1
SIGN_BIT_OUT10: IC10.16 (SIGN_BIT_OUT), SJ56.1
SIGN_BIT_OUT11: IC11.16 (SIGN_BIT_OUT), SJ62.1
SIGN_BIT_OUT12: IC12.16 (SIGN_BIT_OUT), SJ68.1
SIGN_BIT_OUT13: IC13.16 (SIGN_BIT_OUT), SJ74.1
SIGN_BIT_OUT14: IC16.16 (SIGN_BIT_OUT), SJ92.1
SIGN_BIT_OUT15: IC14.16 (SIGN_BIT_OUT), SJ80.1
SIGN_BIT_OUT16: IC17.16 (SIGN_BIT_OUT), SJ98.1
SLEEP_A: IC1.12 (SLEEP), IC2.12 (SLEEP), IC3.12 (SLEEP), IC4.12 (SLEEP), J2.15
SLEEP_B: IC5.12 (SLEEP), IC6.12 (SLEEP), IC7.12 (SLEEP), IC8.12 (SLEEP), J4.13
SLEEP_C: IC9.12 (SLEEP), IC10.12 (SLEEP), IC11.12 (SLEEP), IC12.12 (SLEEP), J1.13
SLEEP_D: IC13.12 (SLEEP), IC14.12 (SLEEP), IC16.12 (SLEEP), IC17.12 (SLEEP), J7.15
VNEG_1: C90.2, C106.1, U1.1 (OUT), U2.2 (GND), U3.4 (VSS)
VNEG_2: C117.2, C119.1, U7.1 (OUT), U8.4 (VSS), U9.2 (GND)
VNEG_3: C141.2, C143.1, U16.1 (OUT), U17.4 (VSS), U18.2 (GND)
VNEG_4: C149.2, C151.1, U19.1 (OUT), U20.4 (VSS), U21.2 (GND)
VNEG_5: C125.2, C127.1, U10.1 (OUT), U11.4 (VSS), U12.2 (GND)
VNEG_6: C133.2, C135.1, U13.1 (OUT), U14.4 (VSS), U15.2 (GND)
VNEG_7: C157.2, C159.1, U22.1 (OUT), U23.4 (VSS), U24.2 (GND)
VNEG_8: C165.2, C167.1, U25.1 (OUT), U26.4 (VSS), U27.2 (GND)
VNEG_9: C173.2, C175.1, U28.1 (OUT), U29.4 (VSS), U30.2 (GND)
VNEG_10: C181.2, C183.1, U31.1 (OUT), U32.4 (VSS), U33.2 (GND)
VNEG_11: C205.2, C207.1, U40.1 (OUT), U41.4 (VSS), U42.2 (GND)
VNEG_12: C213.2, C215.1, U43.1 (OUT), U44.4 (VSS), U45.2 (GND)
VNEG_13: C189.2, C191.1, U34.1 (OUT), U35.4 (VSS), U36.2 (GND)
VNEG_14: C197.2, C199.1, U37.1 (OUT), U38.4 (VSS), U39.2 (GND)
VNEG_15: C221.2, C223.1, U46.1 (OUT), U47.4 (VSS), U48.2 (GND)
VNEG_16: C229.2, C231.1, U49.1 (OUT), U50.4 (VSS), U51.2 (GND)

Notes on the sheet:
Direct Digital Synthesizer (DDS) stages
Variable Gain Amplifier (VGA) stages
Connections to signal distribution board (part of controller board)
Digital Signal Processing (DSP) board

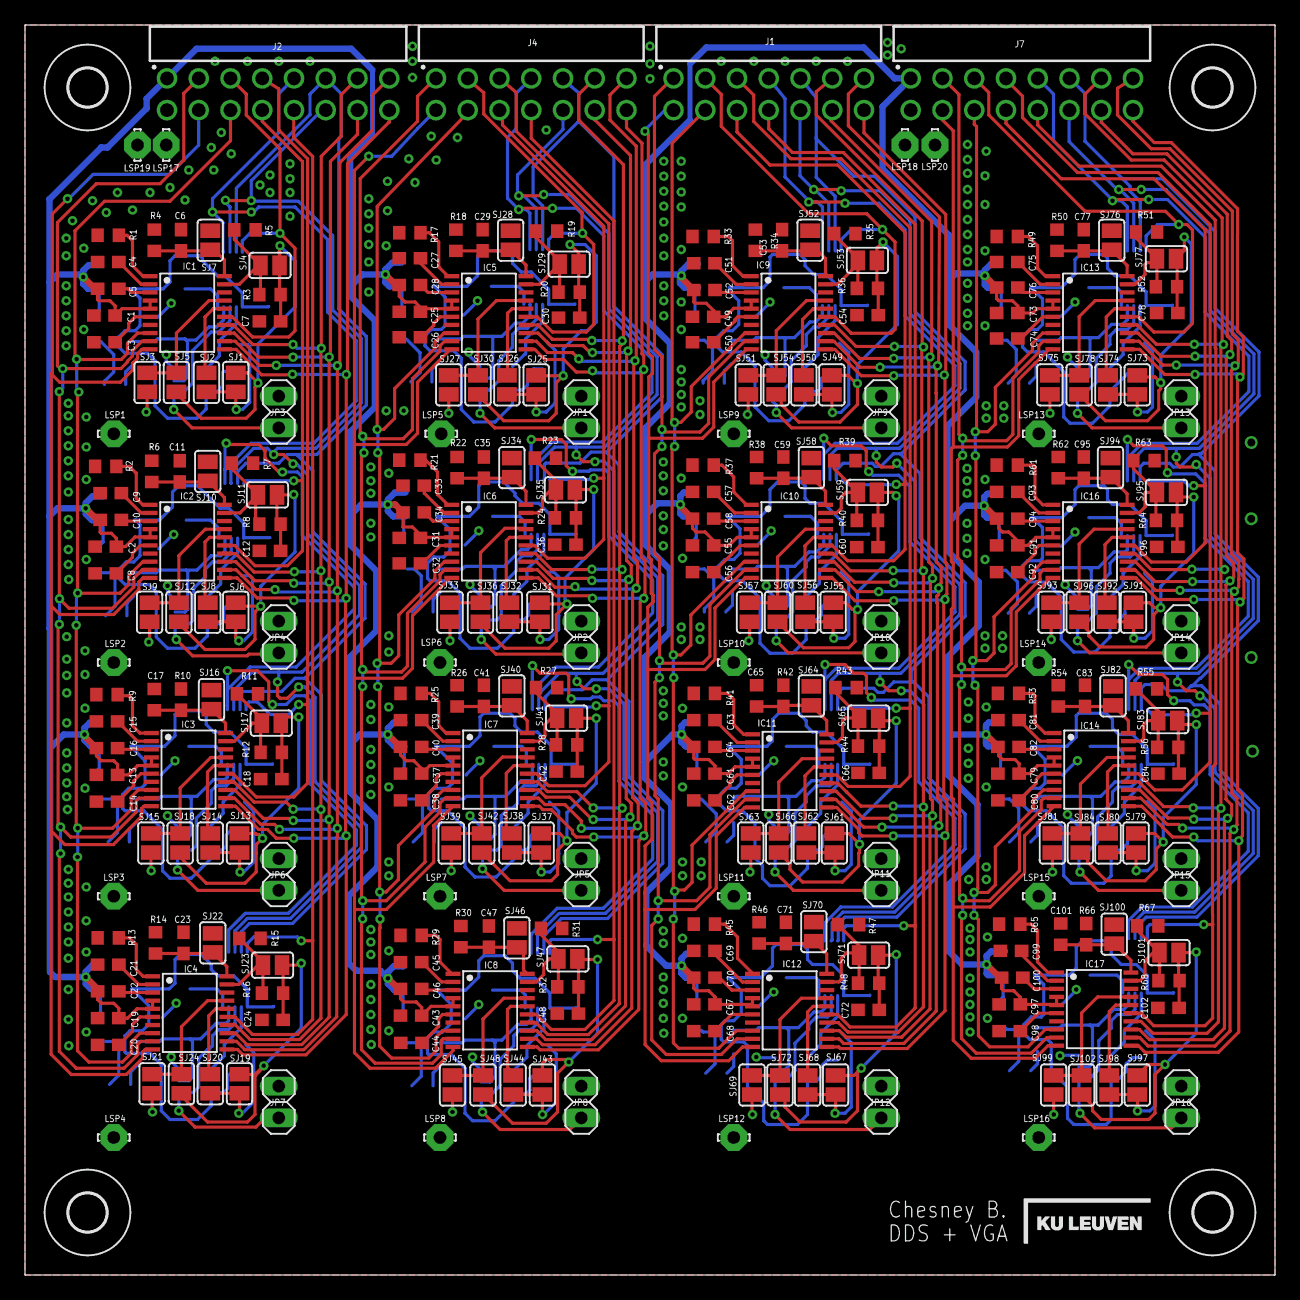
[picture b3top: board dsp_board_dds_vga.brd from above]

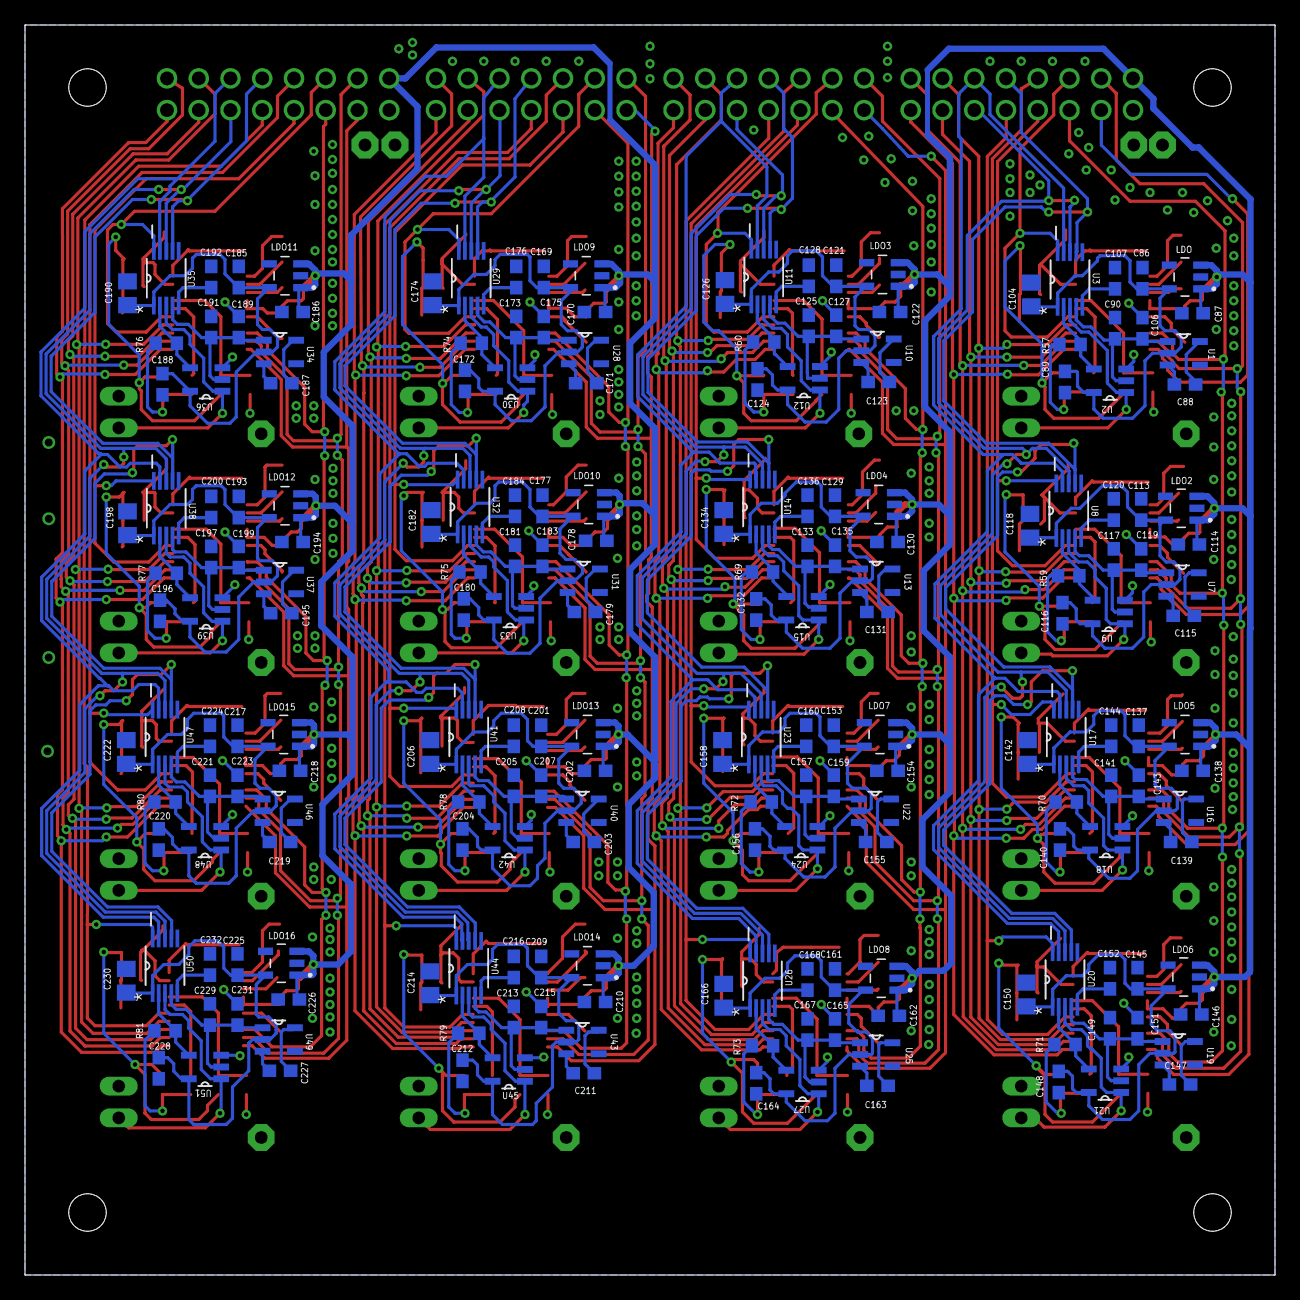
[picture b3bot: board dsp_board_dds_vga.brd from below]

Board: 2 copper layers, 100.0 x 100.0 mm, 524 parts (208 on the bottom side), 330 nets.

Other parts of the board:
H3, H4: MOUNT-HOLE3.0; 3,0

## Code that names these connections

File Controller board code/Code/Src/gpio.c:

/**
  ******************************************************************************
  * File Name          : gpio.c
  * Description        : This file provides code for the configuration
  *                      of all used GPIO pins.
  ******************************************************************************
  * @attention
  *
  * <h2><center>&copy; Copyright (c) 2021 STMicroelectronics.
  * All rights reserved.</center></h2>
  *
  * This software component is licensed by ST under Ultimate Liberty license
  * SLA0044, the "License"; You may not use this file except in compliance with
  * the License. You may obtain a copy of the License at:
  *                             www.st.com/SLA0044
  *
  ******************************************************************************
  */

/* Includes ------------------------------------------------------------------*/
#include "gpio.h"
/* USER CODE BEGIN 0 */

/* USER CODE END 0 */

/*----------------------------------------------------------------------------*/
/* Configure GPIO                                                             */
/*----------------------------------------------------------------------------*/
/* USER CODE BEGIN 1 */

/* USER CODE END 1 */

/** Configure pins
     PC14-OSC32_IN (OSC32_IN)   ------> RCC_OSC32_IN
     PC15-OSC32_OUT (OSC32_OUT)   ------> RCC_OSC32_OUT
     PH0-OSC_IN (PH0)   ------> RCC_OSC_IN
     PH1-OSC_OUT (PH1)   ------> RCC_OSC_OUT
     PC1   ------> ETH_MDC
     PA1   ------> ETH_REF_CLK
     PA2   ------> ETH_MDIO
     PC4   ------> ETH_RXD0
     PC5   ------> ETH_RXD1
     PB13   ------> ETH_TXD1
     PG11   ------> ETH_TX_EN
     PG13   ------> ETH_TXD0
*/
void MX_GPIO_Init(void)
{

  GPIO_InitTypeDef GPIO_InitStruct = {0};

  /* GPIO Ports Clock Enable */
  __HAL_RCC_GPIOE_CLK_ENABLE();
  __HAL_RCC_GPIOC_CLK_ENABLE();
  __HAL_RCC_GPIOF_CLK_ENABLE();
  __HAL_RCC_GPIOH_CLK_ENABLE();
  __HAL_RCC_GPIOA_CLK_ENABLE();
  __HAL_RCC_GPIOB_CLK_ENABLE();
  __HAL_RCC_GPIOG_CLK_ENABLE();
  __HAL_RCC_GPIOD_CLK_ENABLE();

  /*Configure GPIO pin Output Level */
  HAL_GPIO_WritePin(GPIOE, S1_M4A_Pin|FSELECT_Pin|LD2_Pin, GPIO_PIN_RESET);

  /*Configure GPIO pin Output Level */
  HAL_GPIO_WritePin(MUX_EN_B_GPIO_Port, MUX_EN_B_Pin, GPIO_PIN_SET);

  /*Configure GPIO pin Output Level */
  HAL_GPIO_WritePin(GPIOA, PSELECT_Pin|S1_M16A15_Pin, GPIO_PIN_RESET);

  /*Configure GPIO pin Output Level */
  HAL_GPIO_WritePin(GPIOB, LD1_Pin|S0_M16_Pin|LD3_Pin|S1_M16_Pin
                          |S3_M16_Pin, GPIO_PIN_RESET);

  /*Configure GPIO pin Output Level */
  HAL_GPIO_WritePin(GPIOG, S0_M16_B_Pin|S1_M16_B_Pin, GPIO_PIN_RESET);

  /*Configure GPIO pin Output Level */
  HAL_GPIO_WritePin(GPIOD, USB_OTG_FS_PWR_EN_Pin|S0_M4A_Pin|S3_M16_B_Pin|S2_M16_B_Pin, GPIO_PIN_RESET);

  /*Configure GPIO pin Output Level */
  HAL_GPIO_WritePin(S2_M16_GPIO_Port, S2_M16_Pin, GPIO_PIN_RESET);

  /*Configure GPIO pin Output Level */
  HAL_GPIO_WritePin(RESET_GPIO_Port, RESET_Pin, GPIO_PIN_SET);

  /*Configure GPIO pin Output Level */
  HAL_GPIO_WritePin(SLEEP_GPIO_Port, SLEEP_Pin, GPIO_PIN_SET);

  /*Configure GPIO pin Output Level */
  HAL_GPIO_WritePin(MUX_EN_GPIO_Port, MUX_EN_Pin, GPIO_PIN_SET);

  /*Configure GPIO pins : PEPin PEPin PEPin */
  GPIO_InitStruct.Pin = S1_M4A_Pin|FSELECT_Pin|LD2_Pin;
  GPIO_InitStruct.Mode = GPIO_MODE_OUTPUT_PP;
  GPIO_InitStruct.Pull = GPIO_NOPULL;
  GPIO_InitStruct.Speed = GPIO_SPEED_FREQ_LOW;
  HAL_GPIO_Init(GPIOE, &GPIO_InitStruct);

  /*Configure GPIO pin : PtPin */
  GPIO_InitStruct.Pin = B1_Pin;
  GPIO_InitStruct.Mode = GPIO_MODE_INPUT;
  GPIO_InitStruct.Pull = GPIO_NOPULL;
  HAL_GPIO_Init(B1_GPIO_Port, &GPIO_InitStruct);

  /*Configure GPIO pin : PtPin */
  GPIO_InitStruct.Pin = MUX_EN_B_Pin;
  GPIO_InitStruct.Mode = GPIO_MODE_OUTPUT_PP;
  GPIO_InitStruct.Pull = GPIO_NOPULL;
  GPIO_InitStruct.Speed = GPIO_SPEED_FREQ_LOW;
  HAL_GPIO_Init(MUX_EN_B_GPIO_Port, &GPIO_InitStruct);

  /*Configure GPIO pins : PC1 PC4 PC5 */
  GPIO_InitStruct.Pin = GPIO_PIN_1|GPIO_PIN_4|GPIO_PIN_5;
  GPIO_InitStruct.Mode = GPIO_MODE_AF_PP;
  GPIO_InitStruct.Pull = GPIO_NOPULL;
  GPIO_InitStruct.Speed = GPIO_SPEED_FREQ_LOW;
  GPIO_InitStruct.Alternate = GPIO_AF11_ETH;
  HAL_GPIO_Init(GPIOC, &GPIO_InitStruct);

  /*Configure GPIO pins : PAPin PAPin */
  GPIO_InitStruct.Pin = PSELECT_Pin|S1_M16A15_Pin;
  GPIO_InitStruct.Mode = GPIO_MODE_OUTPUT_PP;
  GPIO_InitStruct.Pull = GPIO_NOPULL;
  GPIO_InitStruct.Speed = GPIO_SPEED_FREQ_LOW;
  HAL_GPIO_Init(GPIOA, &GPIO_InitStruct);

  /*Configure GPIO pins : PA1 PA2 */
  GPIO_InitStruct.Pin = GPIO_PIN_1|GPIO_PIN_2;
  GPIO_InitStruct.Mode = GPIO_MODE_AF_PP;
  GPIO_InitStruct.Pull = GPIO_NOPULL;
  GPIO_InitStruct.Speed = GPIO_SPEED_FREQ_LOW;
  GPIO_InitStruct.Alternate = GPIO_AF11_ETH;
  HAL_GPIO_Init(GPIOA, &GPIO_InitStruct);

  /*Configure GPIO pins : PBPin PBPin PBPin PBPin
                           PBPin PBPin */
  GPIO_InitStruct.Pin = LD1_Pin|S0_M16_Pin|LD3_Pin|S1_M16_Pin
                          |MUX_EN_Pin|S3_M16_Pin;
  GPIO_InitStruct.Mode = GPIO_MODE_OUTPUT_PP;
  GPIO_InitStruct.Pull = GPIO_NOPULL;
  GPIO_InitStruct.Speed = GPIO_SPEED_FREQ_LOW;
  HAL_GPIO_Init(GPIOB, &GPIO_InitStruct);

  /*Configure GPIO pins : PGPin PGPin */
  GPIO_InitStruct.Pin = S0_M16_B_Pin|S1_M16_B_Pin;
  GPIO_InitStruct.Mode = GPIO_MODE_OUTPUT_PP;
  GPIO_InitStruct.Pull = GPIO_NOPULL;
  GPIO_InitStruct.Speed = GPIO_SPEED_FREQ_LOW;
  HAL_GPIO_Init(GPIOG, &GPIO_InitStruct);

  /*Configure GPIO pin : PB13 */
  GPIO_InitStruct.Pin = GPIO_PIN_13;
  GPIO_InitStruct.Mode = GPIO_MODE_AF_PP;
  GPIO_InitStruct.Pull = GPIO_NOPULL;
  GPIO_InitStruct.Speed = GPIO_SPEED_FREQ_LOW;
  GPIO_InitStruct.Alternate = GPIO_AF11_ETH;
  HAL_GPIO_Init(GPIOB, &GPIO_InitStruct);

  /*Configure GPIO pins : PDPin PDPin PDPin PDPin
                           PDPin */
  GPIO_InitStruct.Pin = USB_OTG_FS_PWR_EN_Pin|S0_M4A_Pin|S3_M16_B_Pin|S2_M16_B_Pin
                          |SLEEP_Pin;
  GPIO_InitStruct.Mode = GPIO_MODE_OUTPUT_PP;
  GPIO_InitStruct.Pull = GPIO_NOPULL;
  GPIO_InitStruct.Speed = GPIO_SPEED_FREQ_LOW;
  HAL_GPIO_Init(GPIOD, &GPIO_InitStruct);

  /*Configure GPIO pin : PtPin */
  GPIO_InitStruct.Pin = USB_OTG_FS_OVCR_Pin;
  GPIO_InitStruct.Mode = GPIO_MODE_IT_RISING;
  GPIO_InitStruct.Pull = GPIO_NOPULL;
  HAL_GPIO_Init(USB_OTG_FS_OVCR_GPIO_Port, &GPIO_InitStruct);

  /*Configure GPIO pins : PCPin PCPin */
  GPIO_InitStruct.Pin = S2_M16_Pin|RESET_Pin;
  GPIO_InitStruct.Mode = GPIO_MODE_OUTPUT_PP;
  GPIO_InitStruct.Pull = GPIO_NOPULL;
  GPIO_InitStruct.Speed = GPIO_SPEED_FREQ_LOW;
  HAL_GPIO_Init(GPIOC, &GPIO_InitStruct);

  /*Configure GPIO pins : PG11 PG13 */
  GPIO_InitStruct.Pin = GPIO_PIN_11|GPIO_PIN_13;
  GPIO_InitStruct.Mode = GPIO_MODE_AF_PP;
  GPIO_InitStruct.Pull = GPIO_NOPULL;
  GPIO_InitStruct.Speed = GPIO_SPEED_FREQ_LOW;
  GPIO_InitStruct.Alternate = GPIO_AF11_ETH;
  HAL_GPIO_Init(GPIOG, &GPIO_InitStruct);

}

/* USER CODE BEGIN 2 */

/* USER CODE END 2 */

/************************ (C) COPYRIGHT STMicroelectronics *****END OF FILE****/

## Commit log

2021-08-31 Added System Overview
2021-08-31 Updated schematic and board
